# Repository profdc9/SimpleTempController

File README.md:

This is a simple temperature controller based on an Arduino that is intended to be used with an improvised dry heat disinfection unit that operates at 60 to 100 C.  The disinfection unit uses a small metal bucket and lid as the disinfection chamber and incandescent light bulbs as the heating elements which should be available at hardware stores.  The unit is designed to be readily constructible for use in a crisis or pandemic situation where dry heat disinfection is applied to personal protective equipment (PPE).

It is intentionally simple, requiring the minimum specialized parts, so it can be built with parts that are on-hand or readily available.  The main specialized parts are an Arduino Nano or Arduino Uno and a LM35 temperature sensing IC.  The user interface is four LEDs and three push buttons.  A PCB layout is available for a version that uses the Arduino Nano V3.  The PCB is one-sided an a stencil is provided for etching a circuit board.  Because the disinfection unit uses mains power, precautions should be taken to prevent electric shock.

Directories:

-	code: Arduino project
-	doc: Documents describing how to construct and use the improvised dry heat disinfection unit.
- 	SimpleTempController: KiCad PCB layout.  

The PCB was created by Daniel Marks and is available under the Creative Commons CC-BY-SA 4.0 licenses, and the software was also created by Daniel Marks and is available under the zlib license.  THE HARDWARE AND SOFTWARE IS PROVIDED "AS IS", WITHOUT WARRANTY OF ANY KIND, EXPRESS OR IMPLIED, INCLUDING BUT NOT LIMITED TO THE WARRANTIES OF MERCHANTABILITY, FITNESS FOR A PARTICULAR PURPOSE AND NONINFRINGEMENT. IN NO EVENT SHALL THE AUTHORS OR COPYRIGHT HOLDERS BE LIABLE FOR ANY CLAIM, DAMAGES OR OTHER LIABILITY, WHETHER IN AN ACTION OF CONTRACT, TORT OR OTHERWISE, ARISING FROM, OUT OF OR IN CONNECTION WITH THE HARDWARE AND SOFTWARE OR THE USE OR OTHER DEALINGS IN THE HARDWARE AND SOFTWARE.

For any questions, please contact Daniel Marks, profdc9@gmail.com

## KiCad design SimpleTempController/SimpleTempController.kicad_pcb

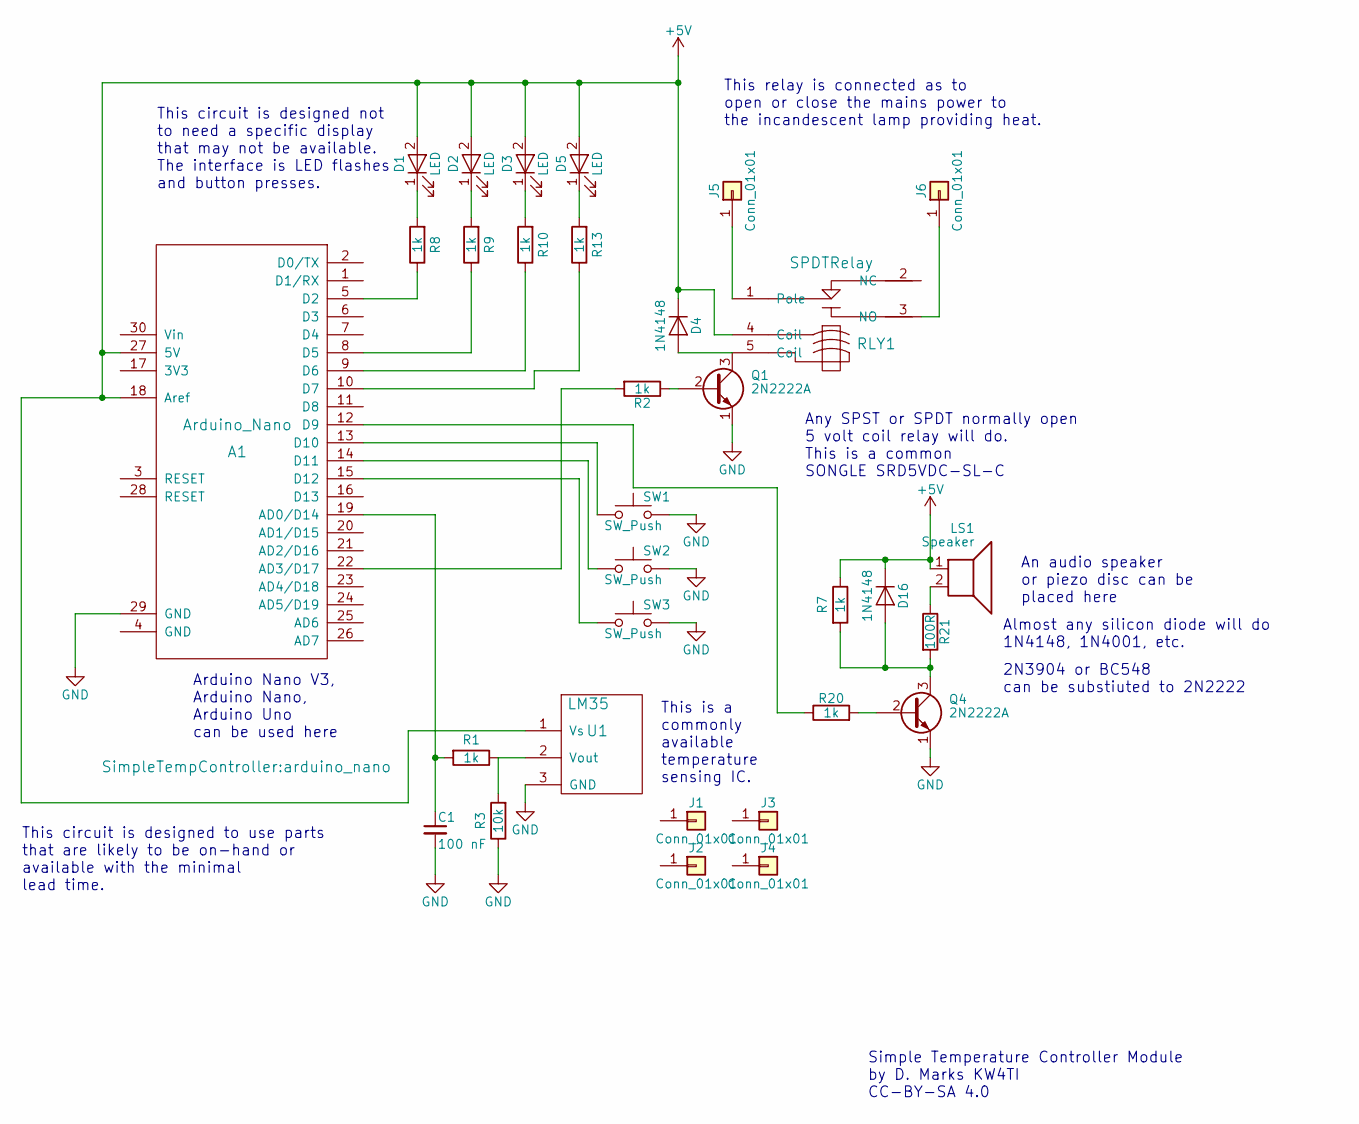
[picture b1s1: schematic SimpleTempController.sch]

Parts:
A1: Arduino_Nano; arduino_nano
C1: 100 nF; C_Disc_D5.0mm_W2.5mm_P5.00mm
D1, D2, D3, D5: LED; LED_D3.0mm
D4, D16: 1N4148; D_DO-41_SOD81_P7.62mm_Horizontal
J1, J2, J3, J4, J5, J6: Conn_01x01; 1pin
LS1: Speaker; TerminalBlock_bornier-2_P5.08mm
Q1, Q4: 2N2222A; TO-92_Molded_Narrow
R1, R2, R7, R8, R9, R10, R13, R20: 1k; R_Axial_DIN0207_L6.3mm_D2.5mm_P7.62mm_Horizontal
R3: 10k; R_Axial_DIN0207_L6.3mm_D2.5mm_P7.62mm_Horizontal
R21: 100R; R_Axial_DIN0207_L6.3mm_D2.5mm_P7.62mm_Horizontal
RLY1: SPDTRelay; SRDXXRelay
SW1, SW2, SW3: SW_Push; SW_PUSH_6mm
U1: LM35; TO-92_Inline_Wide

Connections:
+5V: A1.18 (Aref), A1.27 (5V), D1.2 (A), D2.2 (A), D3.2 (A), D4.1 (K), D5.2 (A), D16.1 (K), LS1.1, R7.1, RLY1.4 (Coil), U1.1 (Vs)
GND: A1.29 (GND), C1.2, Q1.1 (E), Q4.1 (E), R3.1, SW1.2, SW2.2, SW3.2, U1.3 (GND)
unnamed: A1.5 (D2), R8.1
unnamed: A1.8 (D5), R9.1
unnamed: A1.9 (D6), R10.1
unnamed: A1.10 (D7), R13.1
unnamed: A1.12 (D9), R20.1
unnamed: A1.13 (D10), SW1.1
unnamed: A1.14 (D11), SW2.1
unnamed: A1.15 (D12), SW3.1
unnamed: A1.19 (AD0/D14), C1.1, R1.2
unnamed: A1.22 (AD3/D17), R2.2
unnamed: D1.1 (K), R8.2
unnamed: D2.1 (K), R9.2
unnamed: D3.1 (K), R10.2
unnamed: D4.2 (A), Q1.3 (C), RLY1.5 (Coil)
unnamed: D5.1 (K), R13.2
unnamed: D16.2 (A), Q4.3 (C), R7.2, R21.2
unnamed: J5.1, RLY1.1 (Pole)
unnamed: J6.1, RLY1.3 (NO)
unnamed: LS1.2, R21.1
unnamed: Q1.2 (B), R2.1
unnamed: Q4.2 (B), R20.2
unnamed: R1.1, R3.2, U1.2 (Vout)

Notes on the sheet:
Simple Temperature Controller Module by D. Marks KW4TI CC-BY-SA 4.0
Any SPST or SPDT normally open 5 volt coil relay will do. This is a common SONGLE SRD5VDC-SL-C
This relay is connected as to open or close the mains power to the incandescent lamp providing heat.
An audio speaker or piezo disc can be placed here
This circuit is designed not to need a specific display that may not be available. The interface is LED flashes and button presses.
Almost any silicon diode will do 1N4148, 1N4001, etc.
2N3904 or BC548 can be substiuted to 2N2222
Arduino Nano V3, Arduino Nano, Arduino Uno can be used here
This circuit is designed to use parts that are likely to be on-hand or available with the minimal lead time.
This is a commonly available temperature sensing IC.

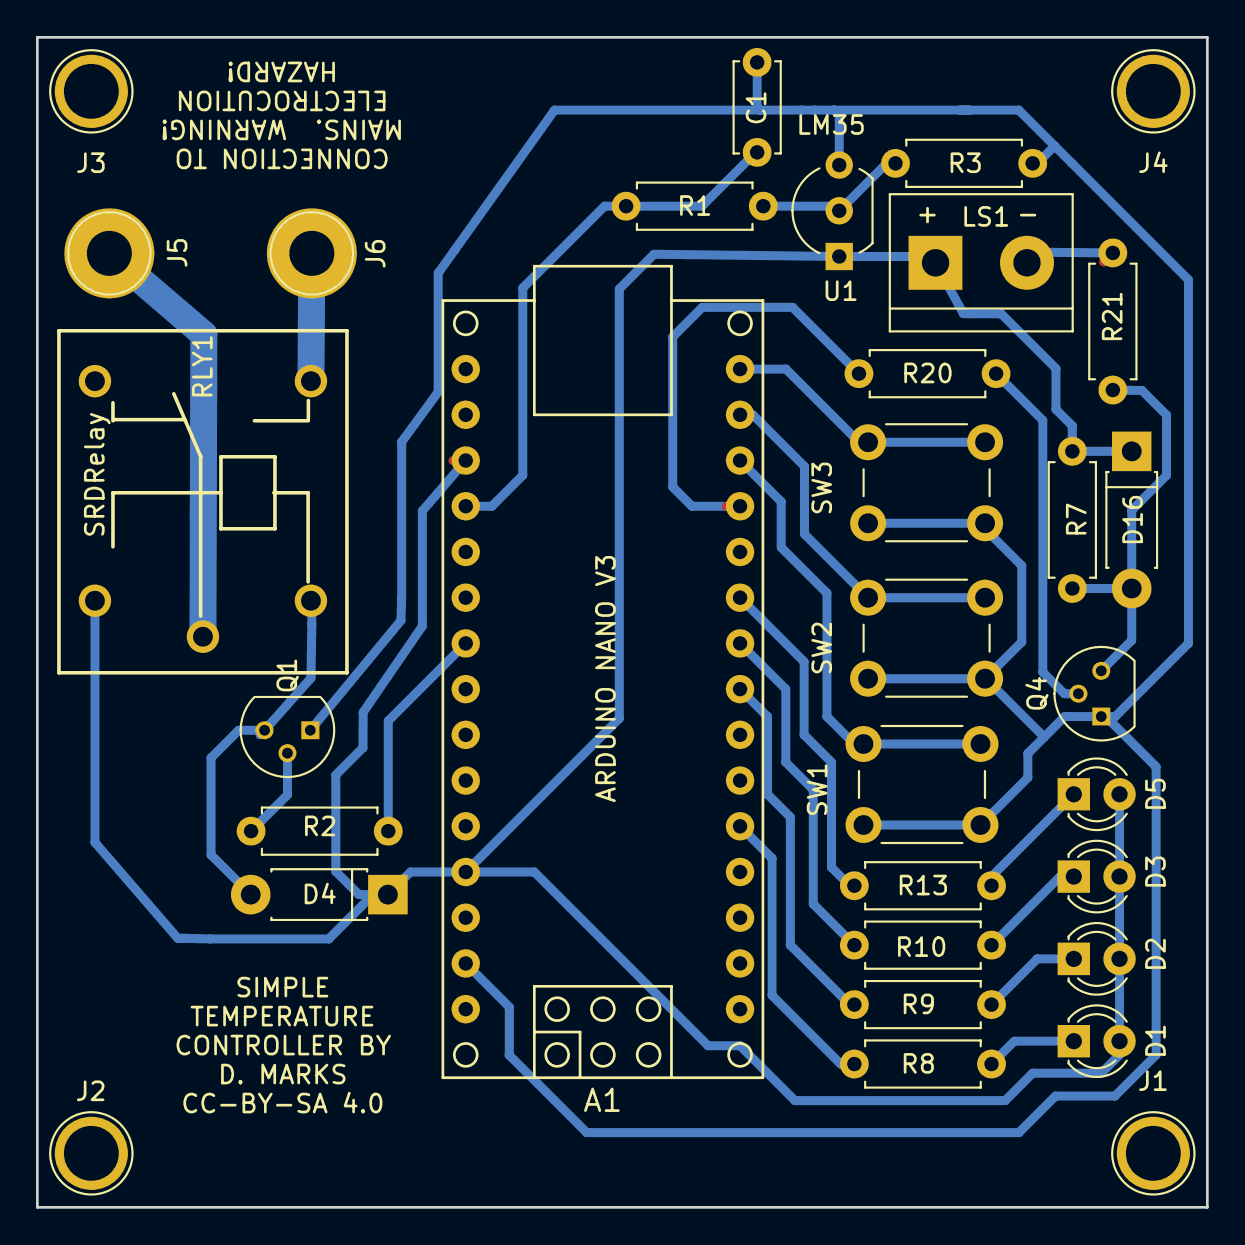
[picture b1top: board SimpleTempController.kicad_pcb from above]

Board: 2 copper layers, 65.0 x 65.0 mm, 32 parts (0 on the bottom side), 24 nets.

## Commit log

2020-04-04 Fixed typo
2020-04-05 Added disclaimer to every page
2020-04-13 More Creepage
2020-04-13 Even more creepage
